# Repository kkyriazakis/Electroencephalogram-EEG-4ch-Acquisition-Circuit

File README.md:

# Electroencephalogram EEG 4CH Acquisition Circuit

## Authors:
* Kleanthis Kyriazakis
* Nicholas John Simos

**This is a project for the course:**
*Special Issues in Electrical Measurement Systems*

Technical University of Crete, 
April 2021

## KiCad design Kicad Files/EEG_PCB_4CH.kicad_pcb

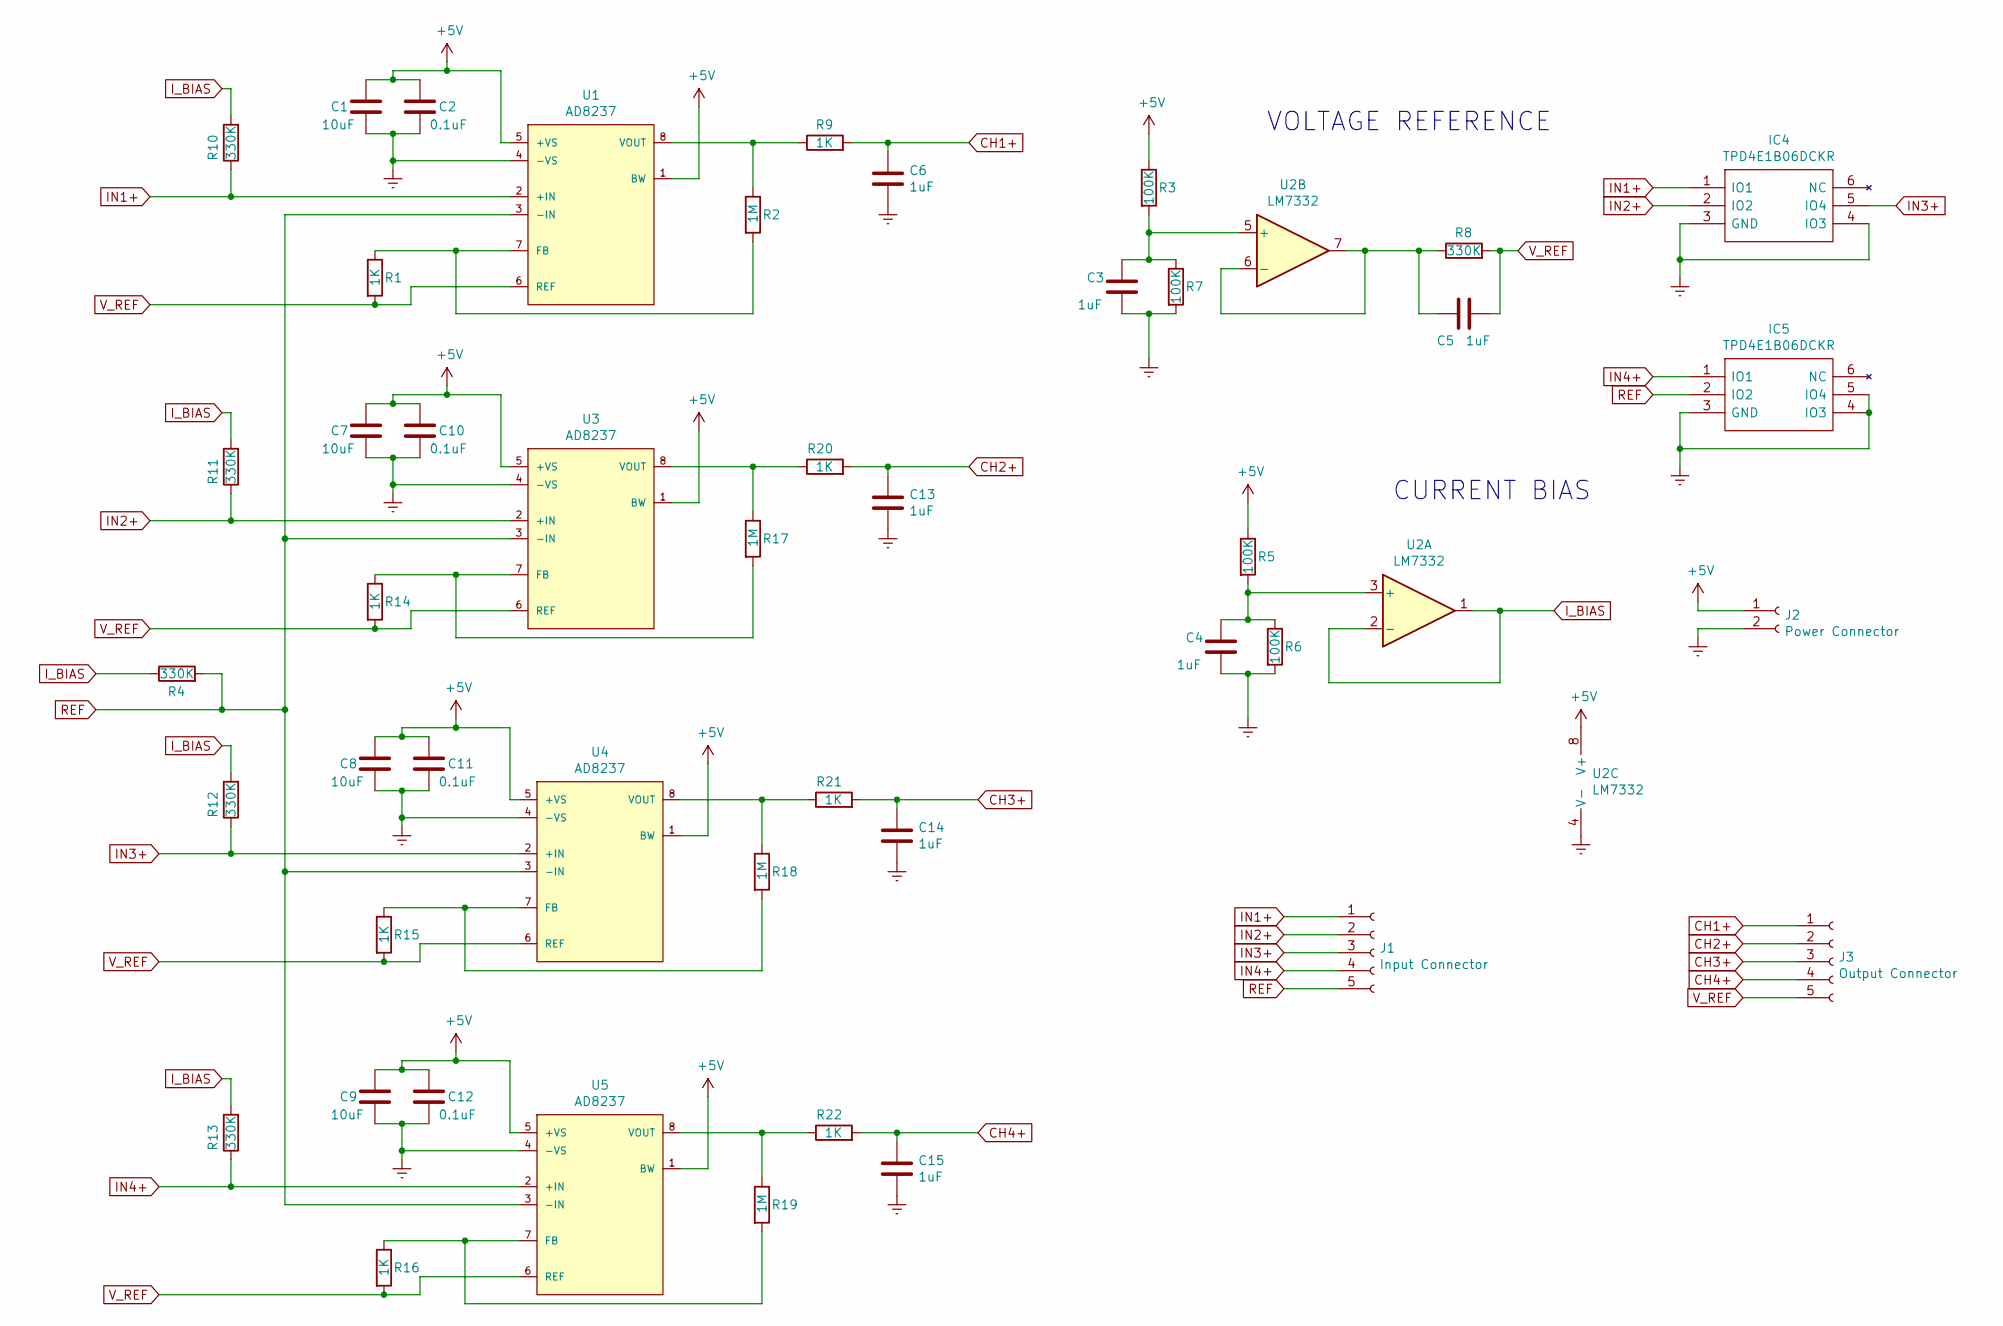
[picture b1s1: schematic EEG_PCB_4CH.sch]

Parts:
C1, C7, C8, C9: 10uF; CP_EIA-1608-08_AVX-J
C2, C10, C11, C12: 0.1uF; CP_EIA-1608-08_AVX-J
C3, C4, C5, C6, C13, C14, C15: 1uF; CP_EIA-1608-08_AVX-J
IC4, IC5: TPD4E1B06DCKR; SOT65P210X110-6N; Manufacturer_Part_Number TPD4E1B06DCKR; Mouser Part Number 595-TPD4E1B06DCKR
J1: Input Connector; PinSocket_1x05_P1.00mm_Vertical
J2: Power Connector; PinSocket_1x02_P2.00mm_Horizontal
J3: Output Connector; PinSocket_1x05_P1.00mm_Vertical
R1, R9, R14, R15, R16, R20, R21, R22: 1K; R_0603_1608Metric
R2, R17, R18, R19: 1M; R_0603_1608Metric
R3, R5, R6, R7: 100K; R_0603_1608Metric
R4, R8, R10, R11, R12, R13: 330K; R_0603_1608Metric
U1, U3, U4, U5: AD8237; Analog_Devices_Inc--0-0-0; mouser part number 584-AD8237ARMZ-R7; digikey description Instrumentation Amplifier 1 Circuit Rai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
U2: LM7332; SOIC127P599X175-8N

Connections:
+5V: C1.1, C2.1, C7.1, C8.1, C9.1, C10.1, C11.1, C12.1, J2.1, R3.1, R5.1, U1.1 (BW), U1.5 (+VS), U2.8 (V+), U3.1 (BW), U3.5 (+VS), U4.1 (BW), U4.5 (+VS), U5.1 (BW), U5.5 (+VS)
CH1+: C6.1, J3.1, R9.2
CH2+: C13.1, J3.2, R20.2
CH3+: C14.1, J3.3, R21.2
CH4+: C15.1, J3.4, R22.2
Earth: C1.2, C2.2, C3.2, C4.2, C6.2, C7.2, C8.2, C9.2, C10.2, C11.2, C12.2, C13.2, C14.2, C15.2, IC4.3 (GND), IC4.4 (IO3), IC5.3 (GND), IC5.4 (IO3), IC5.5 (IO4), J2.2, R6.2, R7.2, U1.4 (-VS), U2.4 (V-), U3.4 (-VS), U4.4 (-VS), U5.4 (-VS)
IN1+: IC4.1 (IO1), J1.1, R10.1, U1.2 (+IN)
IN2+: IC4.2 (IO2), J1.2, R11.1, U3.2 (+IN)
IN3+: IC4.5 (IO4), J1.3, R12.1, U4.2 (+IN)
IN4+: IC5.1 (IO1), J1.4, R13.1, U5.2 (+IN)
I_BIAS: R4.1, R10.2, R11.2, R12.2, R13.2, U2.1, U2.2 (-)
unnamed: C3.1, R3.2, R7.1, U2.5 (+)
unnamed: C4.1, R5.2, R6.1, U2.3 (+)
unnamed: C5.1, R8.1, U2.6 (-), U2.7
unnamed: R1.1, R2.2, U1.7 (FB)
unnamed: R2.1, R9.1, U1.8 (VOUT)
unnamed: R14.1, R17.2, U3.7 (FB)
unnamed: R15.1, R18.2, U4.7 (FB)
unnamed: R16.1, R19.2, U5.7 (FB)
unnamed: R17.1, R20.1, U3.8 (VOUT)
unnamed: R18.1, R21.1, U4.8 (VOUT)
unnamed: R19.1, R22.1, U5.8 (VOUT)
REF: IC5.2 (IO2), J1.5, R4.2, U1.3 (-IN), U3.3 (-IN), U4.3 (-IN), U5.3 (-IN)
V_REF: C5.2, J3.5, R1.2, R8.2, R14.2, R15.2, R16.2, U1.6 (REF), U3.6 (REF), U4.6 (REF), U5.6 (REF)

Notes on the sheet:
VOLTAGE REFERENCE
CURRENT BIAS

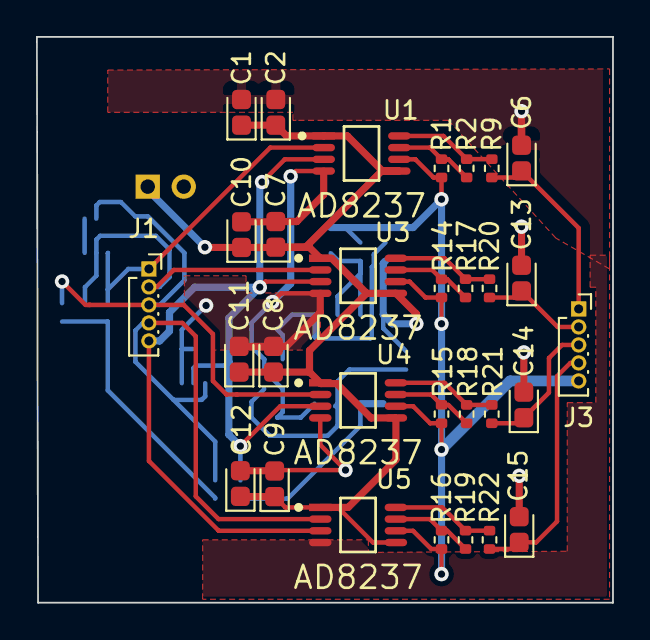
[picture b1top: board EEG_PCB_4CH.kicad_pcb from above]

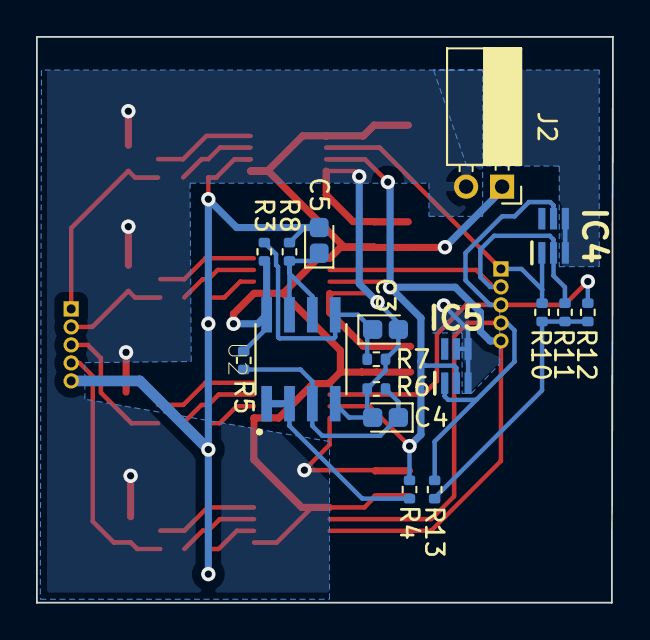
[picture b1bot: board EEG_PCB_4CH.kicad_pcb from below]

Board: 2 copper layers, 32.0 x 31.4 mm, 47 parts (17 on the bottom side), 24 nets.
